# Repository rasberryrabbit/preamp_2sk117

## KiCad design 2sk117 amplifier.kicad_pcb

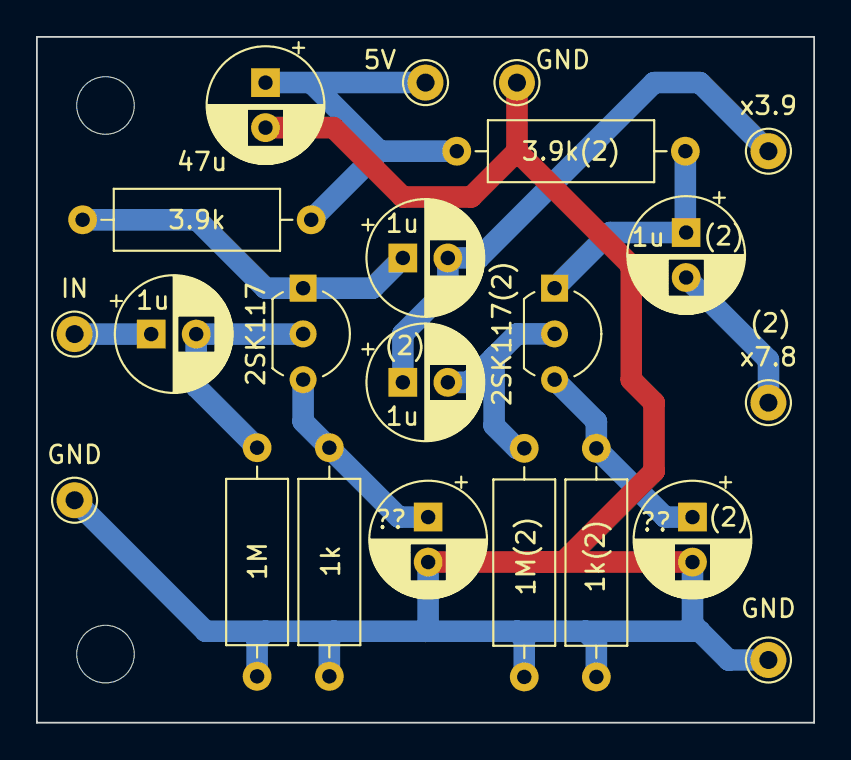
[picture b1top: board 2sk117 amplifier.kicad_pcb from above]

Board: 2 copper layers, 43.2 x 38.1 mm, 22 parts (0 on the bottom side), 11 nets.

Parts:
1M, 1M(2): 1M; R_Axial_DIN0309_L9.0mm_D3.2mm_P12.70mm_Horizontal
1k, 1k(2): 1k; R_Axial_DIN0309_L9.0mm_D3.2mm_P12.70mm_Horizontal
1u, 1u#2, 1u#3, 1u#4: 1u; CP_Radial_D6.3mm_P2.50mm
2SK117, 2SK117(2): 2SK117; TO-92L_Inline_Wide
3.9k, 3.9k(2): 3.9k; R_Axial_DIN0309_L9.0mm_D3.2mm_P12.70mm_Horizontal
5V: VCC; Pin_D1.0mm_L10.0mm
47u: 47u; CP_Radial_D6.3mm_P2.50mm
??: 1u; CP_Radial_D6.3mm_P2.50mm
??#2: 1u; CP_Radial_D6.3mm_P2.50mm
GND: GND; Pin_D1.0mm_L10.0mm
GND#2, GND#3: GND; Pin_D1.0mm_L10.0mm
IN: INPUT; Pin_D1.0mm_L10.0mm
x3.9: OUTPUT3.9; Pin_D1.0mm_L10.0mm
x7.8: OUTPUT7.8; Pin_D1.0mm_L10.0mm

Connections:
unnamed: 1M.2, 1M(2).2, 1k.2, 1k(2).2, 47u.2, ??.2, ??#2.2, GND.1, GND#2.1, GND#3.1
unnamed: 1u#4.1, IN.1
unnamed: 1u.1, 1u#3.2, x3.9.1
unnamed: 1u#2.2, x7.8.1
unnamed: 1u#3.1, 2SK117.1 (D), 3.9k.2
unnamed: 1M.1, 1u#4.2, 2SK117.2 (G)
unnamed: 1k.1, 2SK117.3 (S), ??#2.1
unnamed: 1u#2.1, 2SK117(2).1 (D), 3.9k(2).2
unnamed: 1M(2).1, 1u.2, 2SK117(2).2 (G)
unnamed: 1k(2).1, 2SK117(2).3 (S), ??.1
unnamed: 3.9k.1, 3.9k(2).1, 5V.1, 47u.1

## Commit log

2023-03-17 First.
